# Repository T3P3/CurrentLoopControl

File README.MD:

Control of a 4-20mA current loop with optical isolation by Think3dprint3d and Escher3D

Designed to be connected to Duet Electronics. www.duet3d.com

Licensed under CERN OHL 1.2

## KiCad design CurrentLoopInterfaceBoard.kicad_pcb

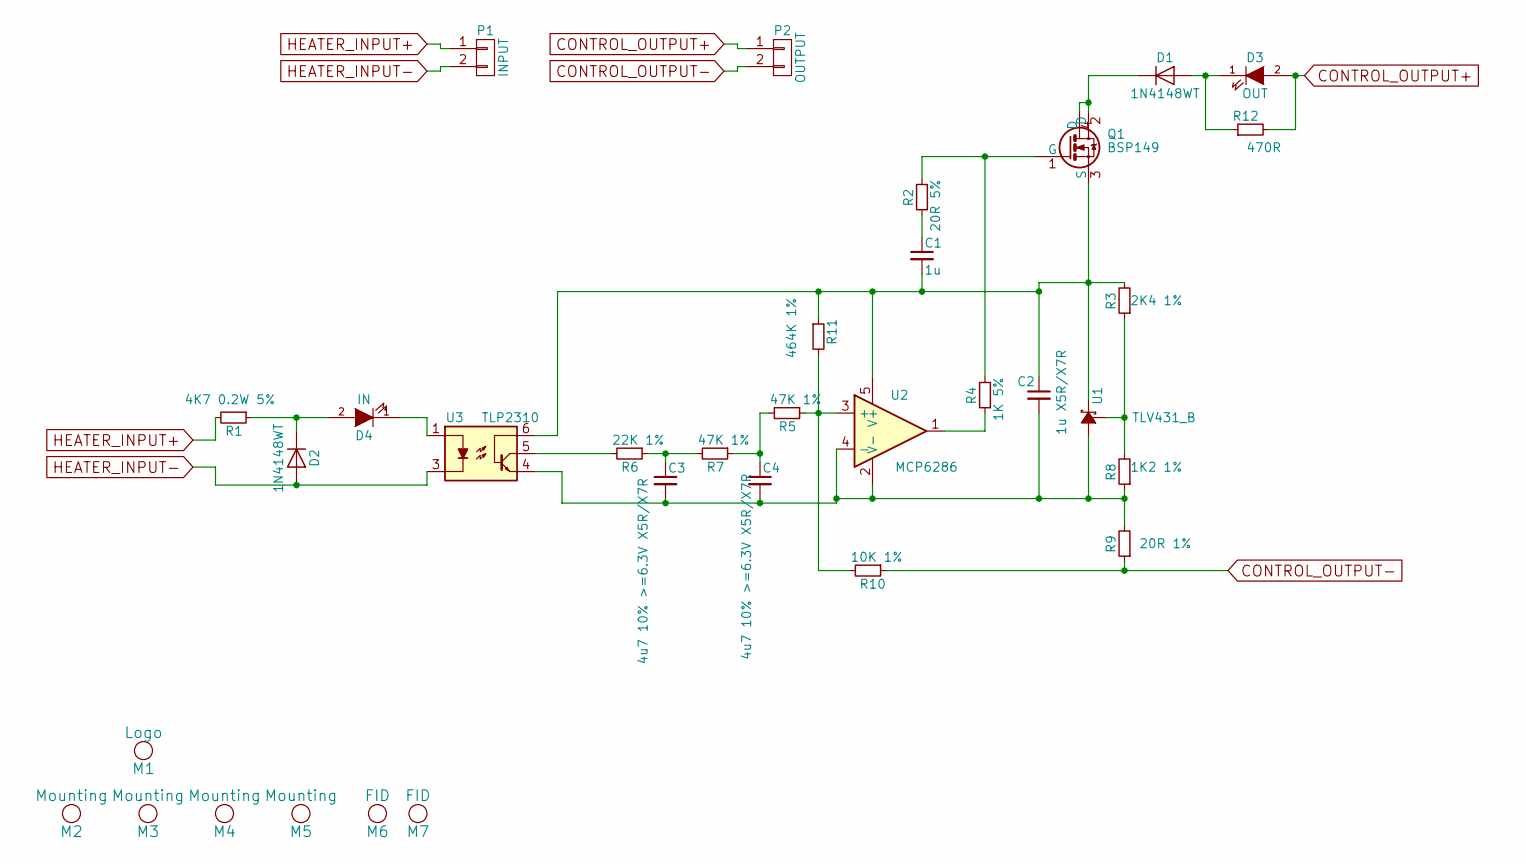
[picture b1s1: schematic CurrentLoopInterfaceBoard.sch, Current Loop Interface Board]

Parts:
C1: 1u; C_0603
C2: 1u X5R/X7R; C_0603
C3, C4: 4u7 10% >=6.3V X5R/X7R; C_0603
D1, D2: 1N4148WT; D_SOD-123F
D3: OUT; LED_0805
D4: IN; LED_0603
M1: Logo; LOGO_Duet3dCompatible_xs
M2, M3, M4, M5: Mounting; Fixing_M3
M6, M7: FID; Fiducial_1mm_Dia_2.54mm_Outer_CopperTop
P1: INPUT; PIN_ARRAY_2X1
P2: OUTPUT; 3.5MM_2X1
Q1: BSP149; SOT-223
R1: 4K7 0.2W 5%; R_0805
R2: 20R 5%; R_0603
R3: 2K4 1%; R_0603
R4: 1K 5%; R_0603
R5, R7: 47K 1%; R_0603
R6: 22K 1%; R_0603
R8: 1K2 1%; R_0603
R9: 20R 1%; R_0603
R10: 10K 1%; R_0603
R11: 464K 1%; R_0603
R12: 470R; R_0603
U1: TLV431_B; SOT-23
U2: MCP6286; SOT-23-5L
U3: TLP2310; SO6_with_5pins

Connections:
CONTROL_OUTPUT+: D3.2 (A), P2.1, R12.2
CONTROL_OUTPUT-: P2.2, R9.1, R10.1
HEATER_INPUT+: P1.1, R1.2
HEATER_INPUT-: D2.2 (A), P1.2, U3.3
unnamed: C1.1, R2.1
unnamed: C1.2, C2.1, Q1.3 (S), R3.2, R11.1, U1.2 (K), U2.5 (V+), U3.6
unnamed: C2.2, C3.2, C4.2, R8.1, R9.2, U1.3 (A), U2.2 (V-), U2.4 (-), U3.4
unnamed: C3.1, R6.1, R7.2
unnamed: C4.1, R5.2, R7.1
unnamed: D1.1 (K), Q1.2 (D), Q1.4 (D)
unnamed: D1.2 (A), D3.1 (K), R12.1
unnamed: D2.1 (K), D4.2 (A), R1.1
unnamed: D4.1 (K), U3.1
unnamed: Q1.1 (G), R2.2, R4.2
unnamed: R3.1, R8.2, U1.1 (Ref)
unnamed: R4.1, U2.1
unnamed: R6.2, U3.5
unnamed: R5.1, R10.2, R11.2, U2.3 (+)

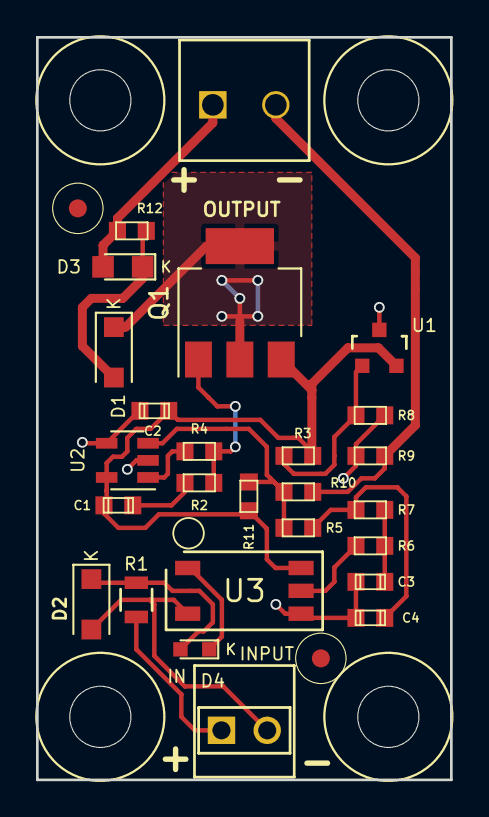
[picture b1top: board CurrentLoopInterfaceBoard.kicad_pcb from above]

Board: 2 copper layers, 23.0 x 41.2 mm, 33 parts (1 on the bottom side), 18 nets.

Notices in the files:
CurrentLoopInterfaceBoard.kicad_pcb:
CERN OHL v1.2
